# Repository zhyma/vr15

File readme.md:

----

## License

本项目基于Creative Commons Attribution 4.0协议开源。

<br />This work is licensed under a <a rel="license" href="http://creativecommons.org/licenses/by/4.0/">Creative Commons Attribution 4.0 International License</a>.

----

# VR15: a VR FPS game controller that generates haptic feedback with high-pressure air.

## <font color="#dd0000">Disclaimer</font>

**This is a VR game controller, a variation of airsoft, not a firearm. It DOES NOT have the ability to shoot any projectile (not even BBs). Although it shares a similar appearance to an AR, it is derived from airsoft, and is NOT compatible with a firearm. The internal is re-designed to accommodate electronic and pneumatic components to generate reoil feedback only. Since it is driven by high-pressure air, please ensure components and their assembly are secured. Replicating and using this design is at your own risk. Please follow your local laws.**

**Disconnect the air source and the power before you disassemble the controller!**

## Implementation

**There are two parts of this project:**

- The hardware design, which is provided in this repository.

- The game that customized for this hardware (as shown in the video/gif). There is a demo made by Unity. You can find it [here](https://github.com/zhyma/rush_b).

## Features

- The haptic feedback is provided by controlled high-pressure air.

- The displacement of the charging handle is being tracked (trigger motion, semi-auto motion, and the magazine is also being tracked).

- Simulate AR's hold open.

- **Check out the full introduction video on Youtube:**

## Design ideas

- A GBB（gas blowback）airsoft uses a mechanical structure to release CO2 or propane to propel BBs and the bolt, which generates reoil feedback. An HPA（high-pressure air）uses a solenoid valve to control the high-pressure air, but usually does not have the bolt design for the sake of power efficiency. For a VR/AR game controller, being able to shoot BBs is not necessary, even harmful. Removing this function can improve safety while playing the game, and improve the generated recoil feedback.

- For the above-mentioned reason, the whole structure can be re-designed (reversed): The gas input coming from the front, pointing directly toward the stock. The solenoid valve can occupy part of the magazine space, then be connected to the cylinder. It is possible to mount the air tank inside of the handguard, if choosing the right size of the air tank.

- Main design purpose: trying to simulate the interaction with an AR as much as possible for a VR scenario.
  - The position tracking of the magazine is done by the VR system (e.g., Oculus Rift). Whether the magazine is well inserted is detected by a microswitch.
  - The displacement of the charging handle is detected by a ToF (time of flight) sensor. Since the handle and the bolt are not always moving together. Whether the bolt is in hold open state is detected by using a Hall sensor.
  - After emptying the magazine,  the bolt catch is driven by an electromagnet to stop the bolt halfway.
  - Safe/fire is achieved by physical design. Pulling the trigger is detected by a microswitch. Semi/auto mode selection is detected by another microswitch.
  - The forward assist is left empty yet. It is possible to install a joystick for interaction.

- Better trigger feedback?

  There are some considerations for using a microswitch to detect the trigger pull:

  1. I want to move the PCB and all electronic components into the trigger box, there is no space for an extra mechanical structure to implement better trigger feedback.
  2. A mechanical trigger weakens the purpose of making a "programmable" controller. The state of the trigger will be determined by the movement of the bolt and the trigger. The controller is not being able to change the state of the trigger, unless you add an extra actuator to move the whole structure (again, not enough space). 

- This design is a proof of concept for a general FPS game controller, the reason for being AR15-alike is because someone gives me a GBB one as the reference. The idea can be applied to (I would say) most rifles. The design can be altered to adapt other "running logic" (as well as the exterior). 

## Possible improvements

- Design an all-in-one PCB that fits the trigger box. So the battery can be installed inside of the pistol grip.
  The ESP32 being used currently is just for prototyping. Replace it with either CC254x, CSR, or some other Bluetooth microcontrollers.

- Add a spring that keeps the bolt catch in place. Currently, if you tilt the controller, it might accidentally move to the hold-open position.

- Add an RFID reader next to the magazine detection switch (maybe the switch can be replaced). Attach RFID tags to magazines. So the VR15 can detect different magazines being inserted (keep tracking the number of the "bullets" in each magazine).

- The animations of ejecting a shell/round and loading a round into the chamber have not been implemented in the game.

- Implement AR's malfunction in the game. Example: a bullet has been fired but failed to extract its shell. In this case, when the player pulls the charging handle to move the bolt, he/she should be able to see the bolt extractor carrying a shell. Or in some cases, the player needs to remove the magazine, pull the charging handle several times to empty the weapon, then do a reload (double feed, maybe?)

- The place for the forward assist is left empty. It might be a good place for a joystick.

- A handguard that can hold the air tank inside.

- The bolt (outside of the cylinder) and the piston spacer should be made of metal. Several reasons:

  1. The bolt is a moving component, should be tough.
  2. They should be heavier for stronger haptic feedback.

- Finding some better solenoid valve (smaller, better fits the upper, higher pressure if possible).

- Tuning 1) the weight of the bolt+piston+buffer, 2) the load of the spring, 3) the input pressure to the valve, 4) the valve opening time.

  I believe those are the major factors that determine the feeling of recoil feedback

- The bolt catch should be made of metal. Plastic is soft and not that durable.

- A pressure gauge connects to the microcontroller. Light up a warning sign when pressure is running low.

## Hardware BOM

### Off-the-shelf parts

- Electronic parts
  
  | Item                   | PCS | Ref image                          | Notes                                                                                |
  | ---------------------- | --- | ---------------------------------- | ------------------------------------------------------------------------------------ |
  | Electromagnet          | 1   |  | 12V，push-and-pull type. The metal frame size is 21x10x11mm, fixing by two M2 screws. |
  | MP1584 DC-DC step down | 1   |             |                                                                                      |
  | ESP32 (WROOM)          | 1   |            |                                                                                      |
  | USB to TTL             | 1   |              | USB to TTL                                                                           |
  | GY6180/VL6180X sensor  | 1   |          | Be aware of the dimensions (There are two sizes, get the smaller one).               |
  | Hall sensor            | 1   |             | The version that outputs an on/off signal (with an amplifier on the board).          |
  | Microswitch KW10-Z3P   | 4   |             |                                                                                      |
  | NMOS SI2302            | 2   |                                    | package: SOT-23. I think 2N7002 also works.                                          |
  | Diode 1N4007           | 2   |                                    | package: SMD (2010?)                                                                 |
  | SMD resistors          | N   |                                    | package：0603. You will need several different values.                                |

- Pneumatic parts（Using Foster 22-2 and NPT 1/8 as an example. You can choose other pneumatic connectors）
  
  | Item                                 | PCS  | Ref image                   | Notes                                                        |
  | ------------------------------------ | ---- | --------------------------- | ------------------------------------------------------------ |
  | Solenoid valve：MAC 35A-AAA-DDBA-1BA | 1    |       | Be aware of the port (NPT or BSPP)<br />You will need to modify its' shell. |
  | Cylinder: MAL16x75                   | 1    |  | You will need to cut one end off.                            |
  | Cylinder: MAL16x25                   | 1    |  | You only need the piston with the guiding rod. You can leave the rest of the parts as a backup. |
  | Foster 22-2 1/8 male NPT x 1/8       | 1    |    | Depending on your air tank output connector.                 |
  | 1/8 NPT female to 1/8 NPT male       | 1+   |   | Being used to extend the Foster connector.                   |
  | 1/8 NPT male M5x0.8 male             | 1    |    | Connect the valve and the cylinder.                          |
  | Air tank (with hose)                 | 1    |                             | I'm using an HPA air tank for airsoft. The output pressure is set to 100psi. |

- Mechanical parts
  
  | Item                         | 数量  | 参考图片                               | 备注                                                                                                                         |
  | ---------------------------- | --- | ---------------------------------- | -------------------------------------------------------------------------------------------------------------------------- |
  | 21 pieces spring and pin set | 1   |    | I think the 32 pieces one contains the magazine release and trigger guard.                                                 |
  | Trigger guard                | 1   |                                    | You can either buy one or 3D print one (like [this](https://www.thingiverse.com/thing:2479358))                            |
  | Magazine release             | 1   |      |                                                                                                                            |
  | Charging handle              | 1   |  | The length is roughly 17mm. Be aware of the size.                                                                          |
  | Buffer and stock set         | 1   |            | Buffer, buffer tube, buffer spring, castle nut, endplate.<br />Stock (I think mk18 navy has plenty of room for batteries). |
  | Pistol grip                  | 1   |         | The one used for GBB, not AEG                                                                                              |
  | Delta ring                   | 1   |       | Not necessary. Or you can [print it](https://www.thingiverse.com/thing:4008338).                                           |

- Standard parts
  
  | Item                            | PCS  | Notes                                       |
  | ------------------------------- | ---- | ------------------------------------------- |
  | M5-0.8x5mm headless screw       | 1    | Seal the input/output of the cylinder.      |
  | M2x15 screws                    | N    | You may need to trim some of those shorter. |
  | M3x6 screw                      | 1    | Fix the GY6180.                             |
  | M3x8 screw                      | 1    | Fix the two-piece upper.                    |
  | M6x20mm screw, washer, and nut. | 1    | Fix the grip.                               |
  | M2.5x16mm screw.                | 1    | Fix the bolt catch.                         |
  | 4mm x 2mm disc magnet           | 1    | Detecting the bolt catch motion.            |

### 3D printed parts 1

| Item                  | PCS  | Ref image                           | Notes                                                        |
| --------------------- | ---- | ----------------------------------- | ------------------------------------------------------------ |
| Lower                 | 1    |             | vr15_lower.STL                                               |
| Upper - left          | 1    |           | vr15_upper_l.STL                                             |
| Upper - right         | 1    |           | vr15_upper_r.STL                                             |
| Trigger box           | 1    |       | trigger_box.STL                                              |
| Trigger               | 1    |           | trigger.STL                                                  |
| Semi-auto selector    | 1    |              | selector.STL                                                 |
| Magazine              | 1    |               | mag.STL (only a placeholder)<br />accessory/oculus_mount/quest_mag_mount.stl: mount Rift/Quest 2 left controller<br />quest_mag_mount_l.stl and quest_mag_mount_r.stl are two-pieces version. |
| Piston spacer         | 1    |            | piston_weight_placeholder.STL<br />You can redesign it (e.g. with copper) to add some weight to enhance the feedback. |
| Piston end            | 1    |              | bolt_plug.STL<br />You can use nuts come with your cylinder. |
| Bolt                  | 1    |       | boltcarrier.STL<br />The original design is using copper to add weight. |
| Bolt catch            | 1    |         | boltcarrier.STL<br />You may need to file it or trim it to make sure it moves smoothly. |
| Charging handle block | 1    |         | charging_handle_block.STL<br />You may need to redesign it to make sure the front of the charging handle is flat. |
| Wire cover            | 1    |  | lower_wire_cover.STL                                         |
| ToF sensor spacer     | 1    |        | tof_spacer.STL                                               |

### 3D printed parts 2

| Item           | PCS | Ref image                         | Notes                                                                                                                                                                                                                                                                                 |
| -------------- | --- | --------------------------------- | ------------------------------------------------------------------------------------------------------------------------------------------------------------------------------------------------------------------------------------------------------------------------------------- |
| delta ring nut | 1   |  | hex_ring.stl<br />You can use a delta ring to fix the front of the upper.                                                                                                                                                                                                             |
| Buffer spacer  | 1   |   | buffer_spacer.STL<br />Make sure your piston won't move out of the cylinder (IMPORTANT!)                                                                                                                                                                                              |
| PCB mount      | 1   |       | pcb_grip_mount.STL                                                                                                                                                                                                                                                                    |
| Quest mount    | 1   |     | You will need  other files from [Thingiverse](https://www.thingiverse.com/thing:3515707)<br />quick_release_picatinny_rail_mount_grip_short<br />quick_release_picatinny_rail_mount_hub<br />quick_release_picatinny_rail_mount_lever_right<br />Mount Rift/Quest 2 right controller. |
| 1/8 NPT plug   | 1   |     | 1_8_npt_plug.STL                                                                                                                                                                                                                                                                      |
| 1/8 NPT plug   | 2   |     | 1_8_npt_side_block.STL                                                                                                                                                                                                                                                                |

## Modify the off-the-shelf parts

### Solenoid valve：

- Use the provided model "1/8 NPT plug" to protect input/output. Remove the protruding part near port No.3. 

- File the corner so the solenoid can be installed into the upper.

- Modify the wire (You can use a JST-XH 2-pin connector.).

### Modify the cylinder：

- Remove the cap of both ends.

- The cap with the rod going through will not be used. For the other one, cut to remove the through-hole. Drill, then tap with M5x0.8. After this modification, the input/output will be located at the top of the cap. Tight the cap back to the cylinder (don't forget your O-ring).

- Now there is one end of the cylinder is left open. Cut near that end to remove the thread, file it to make sure the cut is round and smooth.

- install the piston spacer (it serves as a linear bearing). Using a nut to tighten it up. Then install the rod end.

- Grease the piston and the spacer.

- Install the Foster connector, solenoid valve, and cylinder. (The 1/8 NPT male to the female connector is used to make sure that you can easily connect/disconnect your air source.)

- Use thread seal tape and a headless screw to seal the original input/output in the cylinder.

- Mount the bolt to the rod end. You can use some glue.

### Microswitches：

- You need to modify one of them (for semi-auto selector) a little bit (maybe add a piece of plastic underneath the handle)

- The switch for magazine detection will be installed this way.

### Modify the charging handle

- Glue the charging handle block to the front to make sure the surface toward the TOF sensor is flat.

- You will need to file the L shape end to make sure it can slide into the upper.

- 

## Assembly

### Upper

- Install the TOF sensor. Make sure its' direction is parallel to the handle's movement (you can use the TOF spacer and cut some rubber plate)

- Install the charging handle and pneumatic parts.

- Make sure your wiring is secured.

- The two pieces can be fixed by using screws (3xM2 to the top and )

### Trigger box

- Install the microswitch for mag detection (with two M2 screws).

- Install the microswitches for firing and semi-auto (with two M2 screws).

- Install the electromagnet (with two M2 screws).

- Install the Hall sensor (you can use some hot glue). You adjust the position of the Hall sensor for later steps.

- Install the trigger and its' spring.

- Connect the wires.

### 下机匣

- Install the trigger guards, take-down pins, selector pin, buffer pin, buffer tube to the lower.

- Install the trigger box. fix it with the pin and the magazine release.

- Secure your wires. install the pistol grip (do not tight the screw yet).

- Install the selector (be careful of the little metal handles of the microswitches! )
  Now you can tighten the screw.

- Use epoxy to glue the disc magnet to the bolt catch. Be aware of the polarity. The hall sensor is only sensitive toward one direction.

- Install the bolt catch (with an M2.5 screw). You may need to file or trim it to make sure:
  
  - There is no friction between it and the lower (the electromagnet can move it easily).
  - It moves freely when the upper is installed.
  - It can hold the bolt (the corner that makes contact with the bolt is not so round).
  - It can release the bolt once you press it (the corner that makes contact with the bolt is smooth).

- This is how the bolt catch works:

## PCB

- You can find the schematic, PCB design, and Gerber files in the source file.

- Some soldering. (Move the components from the DC-DC module to the PCB.)
  The PCB was updated after I made this prototype, but has not been tested yet. I made the mistake of using the pins that are connected to the internal flash as GPIO.

- The pinout is shown below.

- There is a model to mount your PCB inside the pistol grip. Wires are TTL (TXD, RXD, GND) and power (11.1V Li-Po)

### Assemble the upper and the lower

- Connect the connectors (ToF sensor and the solenoid valve)

- Place the upper and the lower in place and fix them with the front and rear take-down pins.

## Firmware

- Flash the firmware:
  
  - Turn the switch to "flash" (IO 0 is connected to the GND).
  - Connect TXD to RXD of the USB-TTL board, RXD to TXD, and GND to GND (can't remember whether you should connect the USB first or power up first).

- Use I2C to read VL6180Xdata (Arduino's default setting for ESP32)
  
  - White/IO 22: SCL
  - Green/IO 21: SDA

### Arduino Configuration

- Install VL6180X package (by Pololu，version1.3.0)
- Configure for ESP32
  - Add the address: https://raw.githubusercontent.com/espressif/arduino-esp32/gh-pages/package_esp32_index.json
  - The version I'm using: esp32 by Espressif Systems, version 1.0.4
  - Choose your board: WEMOS LOLIN32 (I only lower the upload speed. I don't think it is necessary.)
    
    ```
    Upload speed: 115200
    CPU frequency: 240MHz(Wifi/BT)
    Flash frequency: 80MHz
    Partition Scheme: Default
    ```

## Communication protocol

### ESP32 to Unity

- 5 bytes, example:
  
  | 1    | 2     | 3     | 4                | 5    |
  | ---- | ----- | ----- | ---------------- | ---- |
  | 0xFA | ToF H | ToF L | Switches' states | 0xAF |

- Start: 0xFA; end: 0xAF

- The 2nd, 3rd byte: ToF data

- The 4th byte: the 5th bit is used to report the solenoid operation is done (from turning on to turning off). The last four bits are used to represent the states of microswitches. 
  
  | 7   | 6   | 5   | 4                                     | 3                                               | 2                                                                | 1                                                                | 0                                              |
  | --- | --- | --- | ------------------------------------- | ----------------------------------------------- | ---------------------------------------------------------------- | ---------------------------------------------------------------- | ---------------------------------------------- |
  | x   | x   | x   | Operating is done<br />"1" is "done". | Hold open<br />"1" is closed.<br />"0" is open. | Magazine inserted<br />"1" is no mag. <br />"0" is mag inserted. | Trigger<br />"1" is trigger pulled<br />"0" is not being pulled. | Semi-auto<br />"1" is auto. <br />"0" is semi. |

### Unity to ESP32

- 1 byte. The first 4 bits are used to control the time of turning on the solenoid. The latter 4 bits are used to decide how long it takes to turn off the electromagnet after turning the solenoid off.
  - Solenoid being turned on for 0 ~ 150ms. Step size: 10ms. The command is 0x0 ~ 0xF.
  - Electromagnet delay is 10 ~ 150ms. Step size: 10ms. The command is 0x1 ~ 0xF. The command 0x0 will not turn on the electromagnet at all.
  - Example: 
    - 0x20 will turn on the solenoid for 20ms, the electromagnet will not be turned on. 
    - 0x2A will turn on the solenoid for 20ms, electromagnet for 120ms (20ms plus 100ms delay).

## Acknowledgment

Big thanks to Tomi, 老吴, Eric, and 检察长！

## Early prototype (with circuit inside of the lower)

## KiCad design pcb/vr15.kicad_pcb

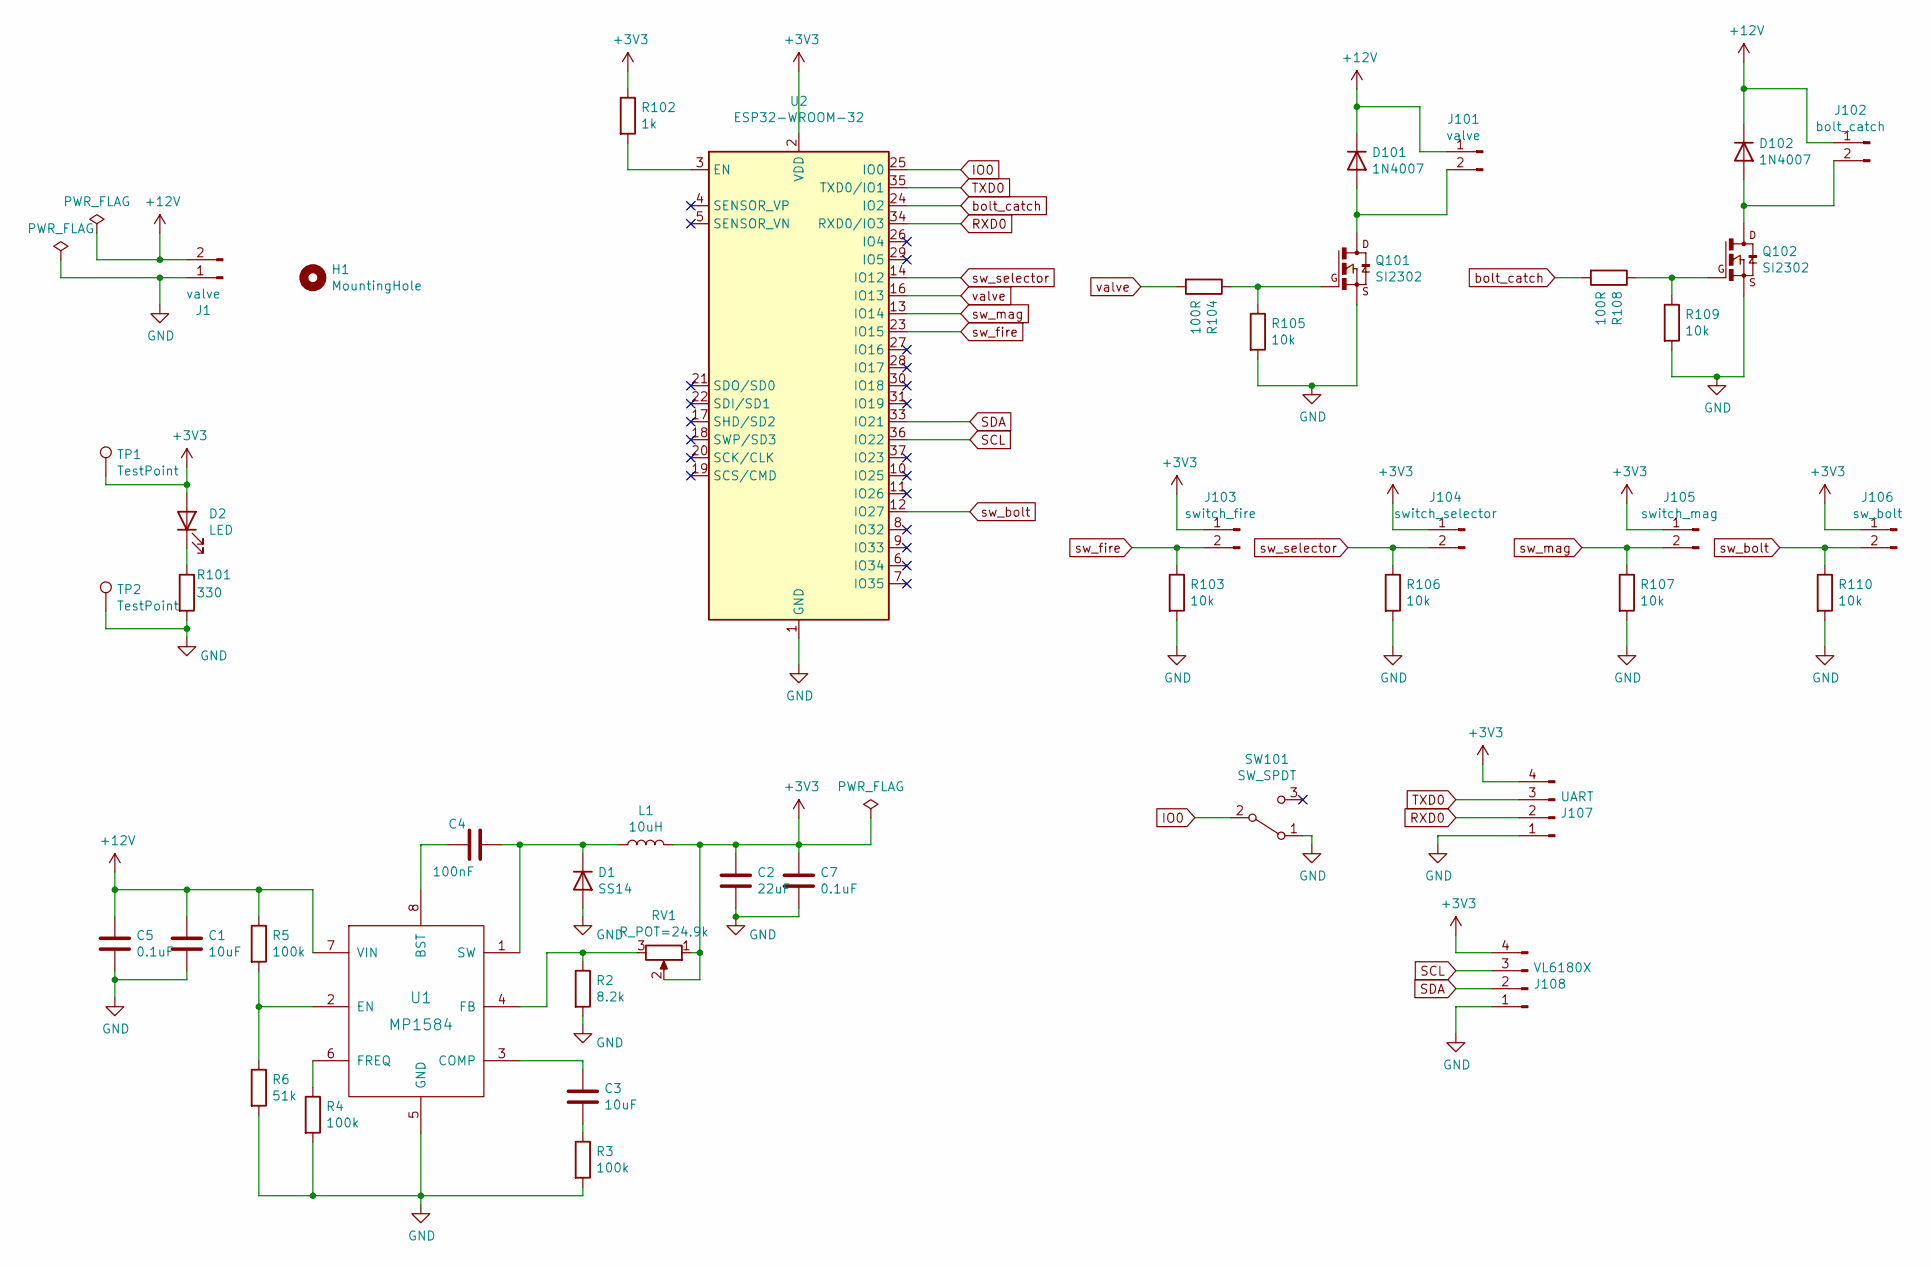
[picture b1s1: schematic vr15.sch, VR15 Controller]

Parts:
C1: 10uF; C_1206_3216Metric_Pad1.33x1.80mm_HandSolder
C2: 22uF; C_1206_3216Metric_Pad1.33x1.80mm_HandSolder
C3: 10uF; C_0603_1608Metric_Pad1.08x0.95mm_HandSolder
C4: 100nF; C_0603_1608Metric_Pad1.08x0.95mm_HandSolder
C5, C7: 0.1uF; C_0603_1608Metric_Pad1.08x0.95mm_HandSolder
D1: SS14; D_2010_5025Metric_Pad1.52x2.65mm_HandSolder
D2: LED; LED_0603_1608Metric_Pad1.05x0.95mm_HandSolder
D101, D102: 1N4007; D_2010_5025Metric_Pad1.52x2.65mm_HandSolder
H1: MountingHole; MountingHole_M2
J1: valve; PinHeader_1x02_P2.54mm_Vertical
J101: valve; PinHeader_1x02_P2.54mm_signal
J102: bolt_catch; PinHeader_1x02_P1.27mm_signal
J103: switch_fire; PinHeader_1x02_P1.27mm_signal
J104: switch_selector; PinHeader_1x02_P1.27mm_signal
J105: switch_mag; PinHeader_1x02_P1.27mm_signal
J106: sw_bolt; PinHeader_1x02_P1.27mm_signal
J107: UART; PinHeader_1x04_P1.27mm_Vertical
J108: VL6180X; PinHeader_1x04_P1.27mm_Vertical
L1: 10uH; L_Vishay_IHLP-2525
Q101, Q102: SI2302; SOT-23
R2: 8.2k; R_0603_1608Metric_Pad0.98x0.95mm_HandSolder
R3, R4, R5: 100k; R_0603_1608Metric_Pad0.98x0.95mm_HandSolder
R6: 51k; R_0603_1608Metric_Pad0.98x0.95mm_HandSolder
R101: 330; R_0603_1608Metric_Pad0.98x0.95mm_HandSolder
R102: 1k; R_0603_1608Metric_Pad0.98x0.95mm_HandSolder
R103, R105, R106, R107, R109, R110: 10k; R_0603_1608Metric_Pad0.98x0.95mm_HandSolder
R104, R108: 100R; R_0603_1608Metric_Pad0.98x0.95mm_HandSolder
RV1: R_POT=24.9k; Potentiometer_Bourns_TC33X_Vertical
SW101: SW_SPDT; SW_SPDT_PCM12
TP1: TestPoint; TestPoint_THTPad_D1.0mm_Drill0.5mm
TP2: TestPoint; TestPoint_THTPad_1.0x1.0mm_Drill0.5mm
U1: MP1584; SOIC-8_3.9x4.9mm_P1.27mm
U2: ESP32-WROOM-32; ESP32-WROOM-32U-simple

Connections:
+3V3: C2.1, C7.1, D2.2 (A), J103.1, J104.1, J105.1, J106.1, J107.4, J108.4, L1.2, R102.1, RV1.1, RV1.2, TP1.1, U2.2 (VDD)
+12V: C1.1, C5.1, D101.1 (K), D102.1 (K), J1.2, J101.1, J102.1, R5.1, U1.7 (VIN)
GND: C1.2, C2.2, C5.2, C7.2, D1.2 (A), J1.1, J107.1, J108.1, Q101.2, Q102.2, R2.2, R3.2, R4.2, R6.2, R101.2, R103.2, R105.2, R106.2, R107.2, R109.2, R110.2, SW101.1 (A), TP2.1, U1.5 (GND), U2.1 (GND), U2.15 (GND), U2.38 (GND)
IO0: SW101.2 (B), U2.25 (IO0)
unnamed: C3.1, U1.3 (COMP)
unnamed: C3.2, R3.1
unnamed: C4.1, U1.8 (BST)
unnamed: C4.2, D1.1 (K), L1.1, U1.1 (SW)
unnamed: D2.1 (K), R101.1
unnamed: D101.2 (A), J101.2, Q101.3
unnamed: D102.2 (A), J102.2, Q102.3
unnamed: Q101.1, R104.1, R105.1
unnamed: Q102.1, R108.1, R109.1
unnamed: R2.1, RV1.3, U1.4 (FB)
unnamed: R4.1, U1.6 (FREQ)
unnamed: R5.2, R6.1, U1.2 (EN)
unnamed: R102.2, U2.3 (EN)
RXD0: J107.2, U2.34 (RXD0/IO3)
SCL: J108.3, U2.36 (IO22)
SDA: J108.2, U2.33 (IO21)
TXD0: J107.3, U2.35 (TXD0/IO1)
bolt_catch: R108.2, U2.24 (IO2)
sw_bolt: J106.2, R110.1, U2.12 (IO27)
sw_fire: J103.2, R103.1, U2.23 (IO15)
sw_mag: J105.2, R107.1, U2.13 (IO14)
sw_selector: J104.2, R106.1, U2.14 (IO12)
valve: R104.2, U2.16 (IO13)

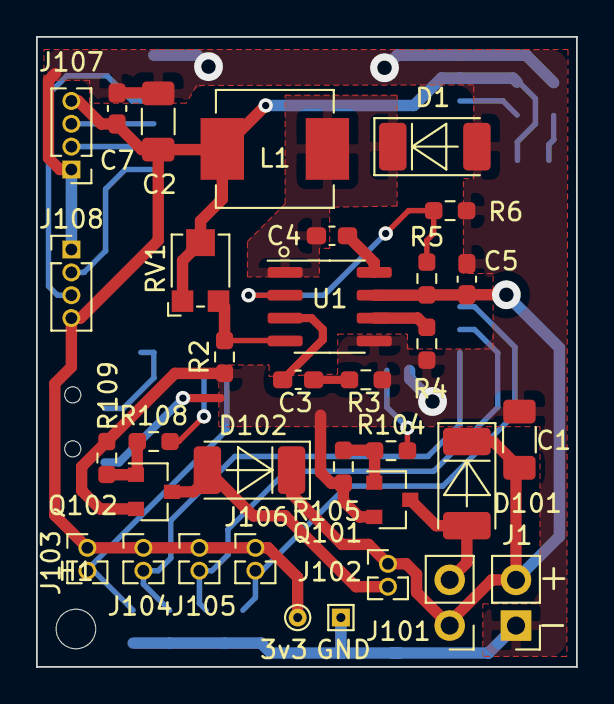
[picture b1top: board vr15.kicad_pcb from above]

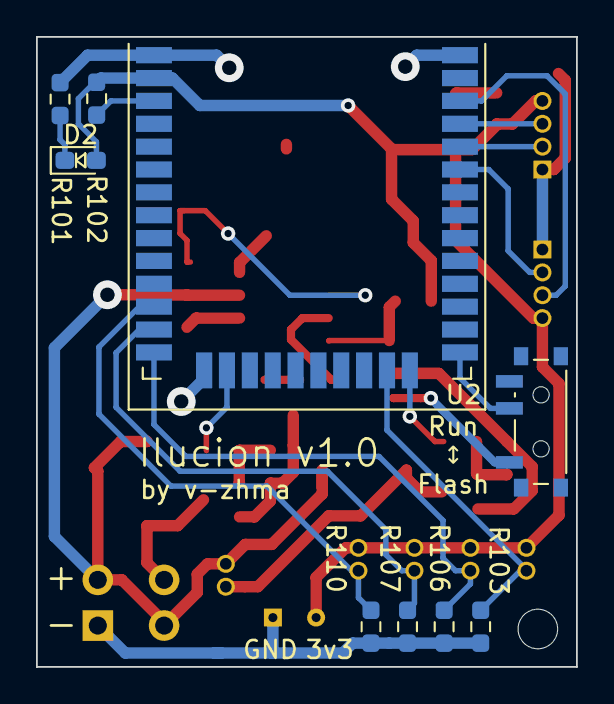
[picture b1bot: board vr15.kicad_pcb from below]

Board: 2 copper layers, 30.0 x 35.0 mm, 44 parts (9 on the bottom side), 27 nets.

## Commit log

2021-12-30 happy new year
